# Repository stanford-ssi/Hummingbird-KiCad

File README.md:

# Hummingbird-KiCad

## Latest Updates

Apr 7, 2025 (Koichi K.): Created the PCB layout. Next steps: figure out power and traces.

Apr 6, 2025 (Sam C.): modified the schematic to be ready for layout. Linked all of the necessary footprints for parts. Added mfr, supplier, cost info. Action item: verification and layout.

Feb 23, 2025 (Victor H., Sam C., Jesse F., Luis S. and Pete!): Modified the KiCad schematic to include correct numbers of PTs, TTs, LCs, etc. (based on P&ID V4). Schematics are organized hierarchically. Problem: Still need to check for input/output conflicts. Action item: can add custom connector footprints next time.

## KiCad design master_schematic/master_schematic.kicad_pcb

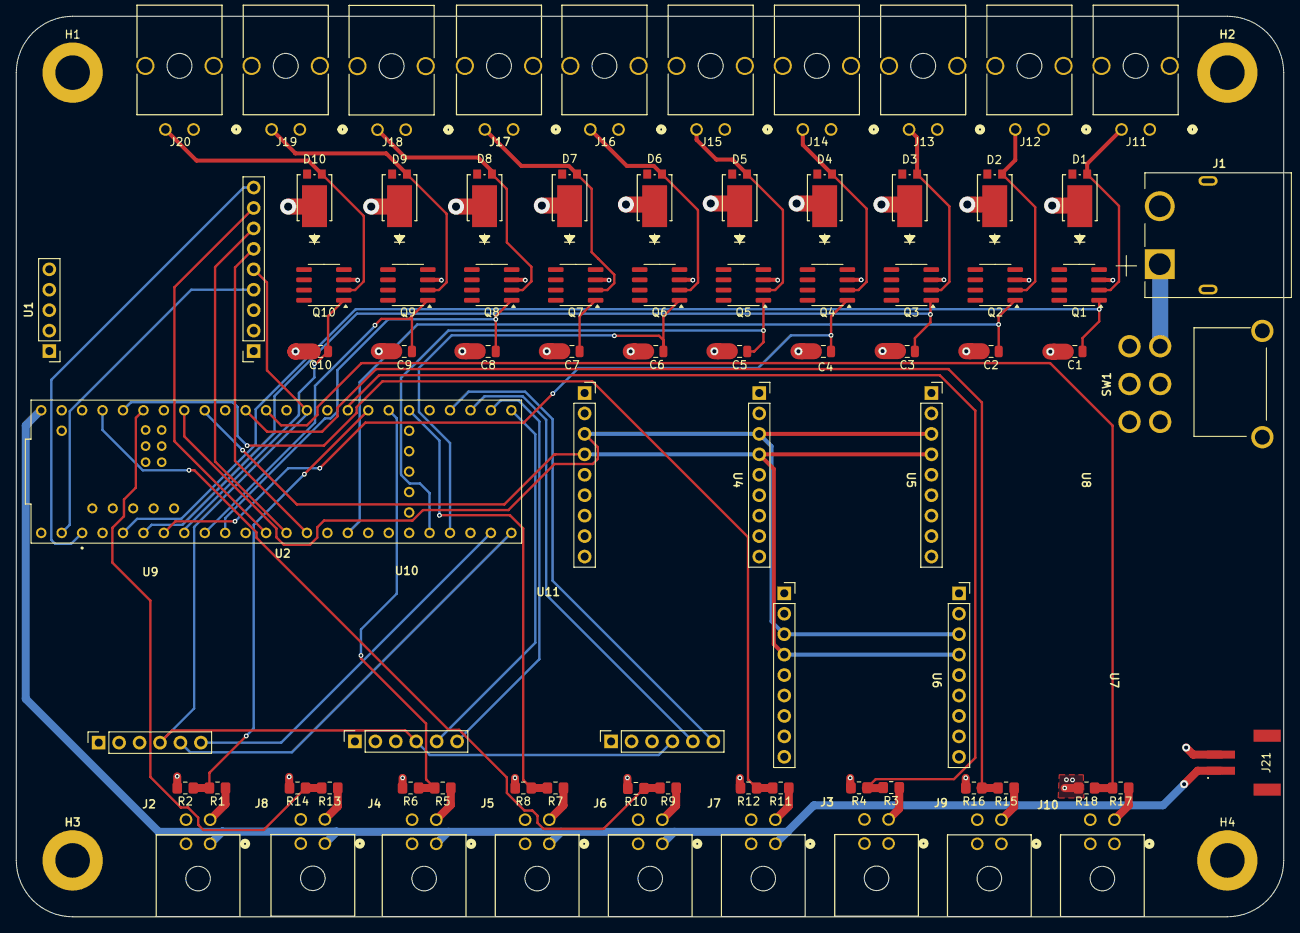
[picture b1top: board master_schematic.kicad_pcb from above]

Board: 4 copper layers, 157.5 x 111.9 mm, 85 parts (0 on the bottom side), 57 nets.

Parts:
C1, C2, C3, C4, C5, C6, C7, C8, C9, C10: 0.1u; C_0805_2012Metric
D1, D2, D3, D4, D5, D6, D7, D8, D9, D10: SBRT20U60SP5-7; POWERDI5_DIO
H1, H2, H3, H4: MountingHole; MountingHole_4.3mm_M4_DIN965_Pad
J1: 12V Female; AMASS_XT60PW-M
J2, J3, J4, J5, J6, J7, J8, J9, J10: 0430450400; CONN_SD-43045-001_04_MOL
J11, J12, J13, J14, J15, J16, J17, J18, J19, J20: 1723103102; CONN02_1723103102_MOL
J21: 5V Female; JST_S2B-PH-SM4-TB
Q1, Q2, Q3, Q4, Q5, Q6, Q7, Q8, Q9, Q10: CWDM3011N TR13 PBFREE; SOIC-8_3.9x4.9mm_P1.27mm
R1, R3, R5, R7, R9, R11, R13, R15, R17: 1K; R_0805_2012Metric_Pad1.20x1.40mm_HandSolder
R2, R4, R6, R8, R10, R12, R14, R16, R18: 2.7K; R_0805_2012Metric_Pad1.20x1.40mm_HandSolder
SW1: SW_SPST; SW_1201M2S3AQE2
SYM1: Logo_Open_Hardware_Large; ssilogo
U1: RFM95; rfm95_connector
U2: teensy_4.1; teensy4.1
U4, U5, U6, U7, U8: MCP9600_Module; mcp9600_connector
U9, U10, U11: HX711; hx711_connector

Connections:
+3V3: U1.1 (VDD), U2.3.3V_1 (3.3V), U2.3.3V_2 (3.3V), U2.3.3V_3 (3.3V), U4.1 (VIN), U5.1 (VIN), U6.1 (VIN), U7.1 (VIN), U8.1 (VIN), U9.1 (VIN), U10.1 (VIN), U11.1 (VIN)
+5V: J2.1 (VDD), J4.1 (VDD), J5.1 (VDD), J6.1 (VDD), J7.1 (VDD), J8.1 (VDD), J21.1, U2.VIN
+12V: D1.1 (K), D2.1 (K), D3.1 (K), D4.1 (K), D5.1 (K), D6.1 (K), D7.1 (K), D8.1 (K), D9.1 (K), D10.1 (K), J3.1 (VDD), J9.1 (VDD), J10.1 (VDD), J11.1, J12.1, J13.1, J14.1, J15.1, J16.1, J17.1, J18.1, J19.1, J20.1, SW1.2 (B)
/BV1-O: C10.1, Q10.1 (G), U2.6 (OUT1D)
/BV1-P: C8.1, Q8.1 (G), U2.8 (TX2)
/BV1-T: C9.1, Q9.1 (G), U2.7 (RX2)
/CS_Radio: U1.8 (CS), U2.10 (CS1)
/IRQ: U1.4 (G0), U2.0 (RX1)
/LC1_DATA: U2.32 (OUT1B), U9.5 (DATA)
/LC1_RATE: U2.31 (CTX3), U9.6 (RATE)
/LC2_DATA: U2.33 (MCLK2), U10.5 (DATA)
/LC2_RATE: U2.34 (RX8), U10.6 (RATE)
/LC3_DATA: U2.35 (TX8), U11.5 (DATA)
/LC3_RATE: U2.36 (CS2), U11.6 (RATE)
/MBV1-I-1: C5.1, Q5.1 (G), U2.28 (RX7)
/MBV1-I-2: C6.1, Q6.1 (G), U2.29 (TX7)
/MISO: U1.6 (MISO), U2.12 (MISO)
/MOSI: U1.7 (MOSI), U2.11 (MOSI)
/PT1_I: R9.2, R10.1, U2.23 (A9)
/PT1_N: R3.2, R4.1, U2.41 (A17)
/PT1_O: R1.2, R2.1, U2.40 (A16)
/PT1_P: R5.2, R6.1, U2.39 (A15)
/PT1_T: R7.2, R8.1, U2.38 (A14)
/PT2_I: R11.2, R12.1, U2.22 (A8)
/PT3_I: R13.2, R14.1, U2.21 (A7)
/PT4_I: R15.2, R16.1, U2.16 (A2)
/PT5_I: R17.2, R18.1, U2.15 (A1)
/PV1_N: C1.1, Q1.1 (G), U2.3 (LRCLK2)
/PV1_O: C2.1, Q2.1 (G), U2.24 (A10)
/PV1_P: C3.1, Q3.1 (G), U2.4 (BCLK2)
/PV1_T: C4.1, Q4.1 (G), U2.5 (IN2)
/PV2_O: C7.1, Q7.1 (G)
/RST: U1.9 (RST), U2.1 (TX1)
/SCK: U1.5 (SCK), U2.13 (SCK), U9.4 (SCK), U10.4 (SCK), U11.4 (SCK)
/SCL: U2.19 (A5), U4.3 (SCL), U5.3 (SCL), U6.3 (SCL), U7.3 (SCL), U8.3 (SCL)
/SDA: U2.18 (A4), U4.4 (SDA), U5.4 (SDA), U6.4 (SDA), U7.4 (SDA), U8.4 (SDA)
/pressure_transducers/PT1_I_RAW: J6.3 (DATA), R9.1
/pressure_transducers/PT1_N_RAW: J3.3 (DATA), R3.1
/pressure_transducers/PT1_O_RAW: J2.3 (DATA), R1.1
/pressure_transducers/PT1_P_RAW: J4.3 (DATA), R5.1
/pressure_transducers/PT1_T_RAW: J5.3 (DATA), R7.1
/pressure_transducers/PT2_I_RAW: J7.3 (DATA), R11.1
/pressure_transducers/PT3_I_RAW: J8.3 (DATA), R13.1
/pressure_transducers/PT4_I_RAW: J9.3 (DATA), R15.1
/pressure_transducers/PT5_I_RAW: J10.3 (DATA), R17.1
GND: C1.2, C2.2, C3.2, C4.2, C5.2, C6.2, C7.2, C8.2, C9.2, C10.2, J1.2, J2.2 (GND), J3.2 (GND), J4.2 (GND), J5.2 (GND), J6.2 (GND), J7.2 (GND), J8.2 (GND), J9.2 (GND), J10.2 (GND), J21.2, Q1.3 (S), Q2.3 (S), Q3.3 (S), Q4.3 (S), Q5.3 (S), Q6.3 (S), Q7.3 (S), Q8.3 (S), Q9.3 (S), Q10.3 (S), R2.2, R4.2, R6.2, R8.2, R10.2, R12.2, R14.2, R16.2, R18.2, U1.2 (GND), U2.GND1 (GND), U2.GND2 (GND), U2.GND3 (GND), U2.GND4 (GND), U2.GND5 (GND), U2.USB_GND1 (USB_GND), U2.USB_GND2 (USB_GND), U4.2 (GND), U5.2 (GND), U6.2 (GND), U7.2 (GND), U8.2 (GND), U9.3 (GND), U10.3 (GND), U11.3 (GND)
unnamed: D1.2 (A), J11.2, Q1.2 (D)
unnamed: D2.2 (A), J12.2, Q2.2 (D)
unnamed: D3.2 (A), J13.2, Q3.2 (D)
unnamed: D4.2 (A), J14.2, Q4.2 (D)
unnamed: D5.2 (A), J15.2, Q5.2 (D)
unnamed: D6.2 (A), J16.2, Q6.2 (D)
unnamed: D7.2 (A), J17.2, Q7.2 (D)
unnamed: D8.2 (A), J18.2, Q8.2 (D)
unnamed: D9.2 (A), J19.2, Q9.2 (D)
unnamed: D10.2 (A), J20.2, Q10.2 (D)
unnamed: J1.1, SW1.1 (A)

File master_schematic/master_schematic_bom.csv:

"Reference","Value","Datasheet","Footprint","Qty","Manufacturer","Manufacturer Part #","Supplier","Supplier Part #","Unit Cost","Cost @ Qty","Manufacturer 2","Manufacturer Part # 2","Supplier 2","Supplier Part # 2","Unit Cost 2","Cost @ Qty 2"
"U2","RFM95","https://learn.adafruit.com/adafruit-rfm69hcw-and-rfm96-rfm95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","hb_footprint_lib:rfm95_connector","1","Sullins Connector Solutions","PPPC091LFBN-RC","Digikey","PPPC091LFBN-RC","0.63","0.63","Sullins Connector Solutions","PPPC051LFBN-RC","Digikey","PPPC051LFBN-RC","0.43","0.43"
"U9,U10,U11","HX711","https://learn.adafruit.com/adafruit-hx711-24-bit-adc","hb_footprint_lib:hx711_connector","3","Sullins Connector Solutions","PPPC061LFBN-RC","Digikey","PPPC061LFBN-RC","0.47","0.47","","","","","",""
"U4,U5,U6,U7,U8","MCP9600_Module","https://learn.adafruit.com/adafruit-mcp9600-i2c-thermocouple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","hb_footprint_lib:mcp9600_connector","5","Sullins Connector Solutions","PPPC091LFBN-RC","Digikey","PPPC091LFBN-RC","0.63","0.63","","","","","",""
"R2,R4,R6,R8,R10,R12,R14,R16,R18","2.7K","https://industrial.panasonic.com/cdbs/www-data/pdf/RDM0000/A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","Resistor_SMD:R_0805_2012Metric_Pad1.20x1.40mm_HandSolder","9","Panasonic Electronic Components","ERJ-6GEYJ272V","Digikey","P2.7KACT-ND","0.10","0.042","","","","","",""
"R1,R3,R5,R7,R9,R11,R13,R15,R17","1K","https://industrial.panasonic.com/cdbs/www-data/pdf/RDM0000/A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","Resistor_SMD:R_0805_2012Metric_Pad1.20x1.40mm_HandSolder","9","Panasonic Electronic Components","ERA-6AEB102V","Digikey","P1.0KDACT-ND","0.10","0.066","","","","","",""
"Q1,Q2,Q3,Q4,Q5,Q6,Q7,Q8,Q9","CWDM3011N TR13 PBFREE","https://my.centralsemi.com/datasheets/CWDM3011N.PDF","Package_SO:SOIC-8_3.9x4.9mm_P1.27mm","9","Central Semiconductor Corp","CWDM3011N TR13 PBFREE","Digikey","1514-CWDM3011NTR13PBFREECT-ND","1.09","1.09","","","","","",""
"J11,J12,J13,J14,J15,J16,J17,J18,J19","1723103102","https://www.molex.com/en-us/products/part-detail/1723103102?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","hb_footprint_lib:CONN02_1723103102_MOL","9","Molex","1723103102","Digikey","900-1723103102-ND","0.85","0.85","","","","","",""
"J2,J3,J4,J5,J6,J7,J8,J9,J10","0430450400","https://tools.molex.com/pdm_docs/ps/PS-43045.pdf","hb_footprint_lib:CONN_SD-43045-001_04_MOL","9","Molex","0430450400","Digikey","WM1814-ND","1.42","1.42","","","","","",""
"J1","Conn_01x02_Shielded","https://www.lcsc.com/datasheet/lcsc_datasheet_2401181031_Cha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","hb_footprint_lib:AMASS_XT60PW-M","1","Changzhou Amass Elec","XT60PW-M","LCSC","C98732","0.59","0.59","","","","","",""
"D1,D2,D3,D4,D5,D6,D7,D8,D9","SBRT20U60SP5-7","https://www.diodes.com/assets/Datasheets/SBRT20U60SP5.pdf","hb_footprint_lib:POWERDI5_DIO","9","Diodes Incorporated","SBRT20U60SP5-7","Digikey","SBRT20U60SP5-7DICT-ND","0.78","0.78","","","","","",""

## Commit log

2024-12-04 Add files via upload
    Added KiCAD files from previous hummingbird repo
2025-01-20 master_schematic update
2025-01-25 added footprint library and a pcb file
2025-02-22 Added symbol libraries for HX711 and the transistor IRLZ34NPBF. Made schematic for solenoid valve.
2025-02-23 added sheet and connections for PT
2025-02-23 gitignore
2025-02-23 PT update
2025-02-24 full master schematic in hierarchical format
2025-02-24 minor updates
2025-04-07 modified for PCB development
2025-04-07 updated with part info
2025-04-08 fixed errors on schematic
2025-04-08 patch fix
2025-04-08 finished building PCB
2025-04-11 updated BOM
2025-04-14 pcb layout and traces made (partially)
2025-04-15 updated BOM materials
2025-04-15 added decoupling capacitors, fixed voltage values for TTs and load cells to +3V3
2025-04-20 finding parts
2025-04-22 edits after bom
2025-04-22 updated schematic for PT
2025-04-22 adding library items
2025-04-22 stuff
2025-04-22 fixed errors, redesigned PCB layout
2025-04-22 redid power layer
2025-05-06 routed some annoying ass traces
2025-05-13 FINALLY FINISHED ThESE DAMN TRACES F&#%%%
2025-06-06 I dont know what change this is lol
2025-06-06 Edited the switch to be in series with the circuit (instead of parallel)
2025-06-06 added logo file
2025-06-06 added bitmap file
2025-06-06 Edited silkscreens
2025-07-31 Initial plan
2025-07-31 Add comprehensive repository structure and functionality summary
